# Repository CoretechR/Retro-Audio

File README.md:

# DIY Retro Audio Player

Inspired by 1980s tape recorders, this audio player was designed with ease of use and accessibility in mind. Despite its nostalgic appearance, it packs modern hardware. Powered by the ESP32, it plays music and audiobooks from a micro SD card, either on its internal speaker or though a headphone jack. A 2.8“ IPS screen and mechanical buttons make up the simplistic user interface. The software is built around the ESP32-audioI2S library by GitHub user Schreibfaul1.

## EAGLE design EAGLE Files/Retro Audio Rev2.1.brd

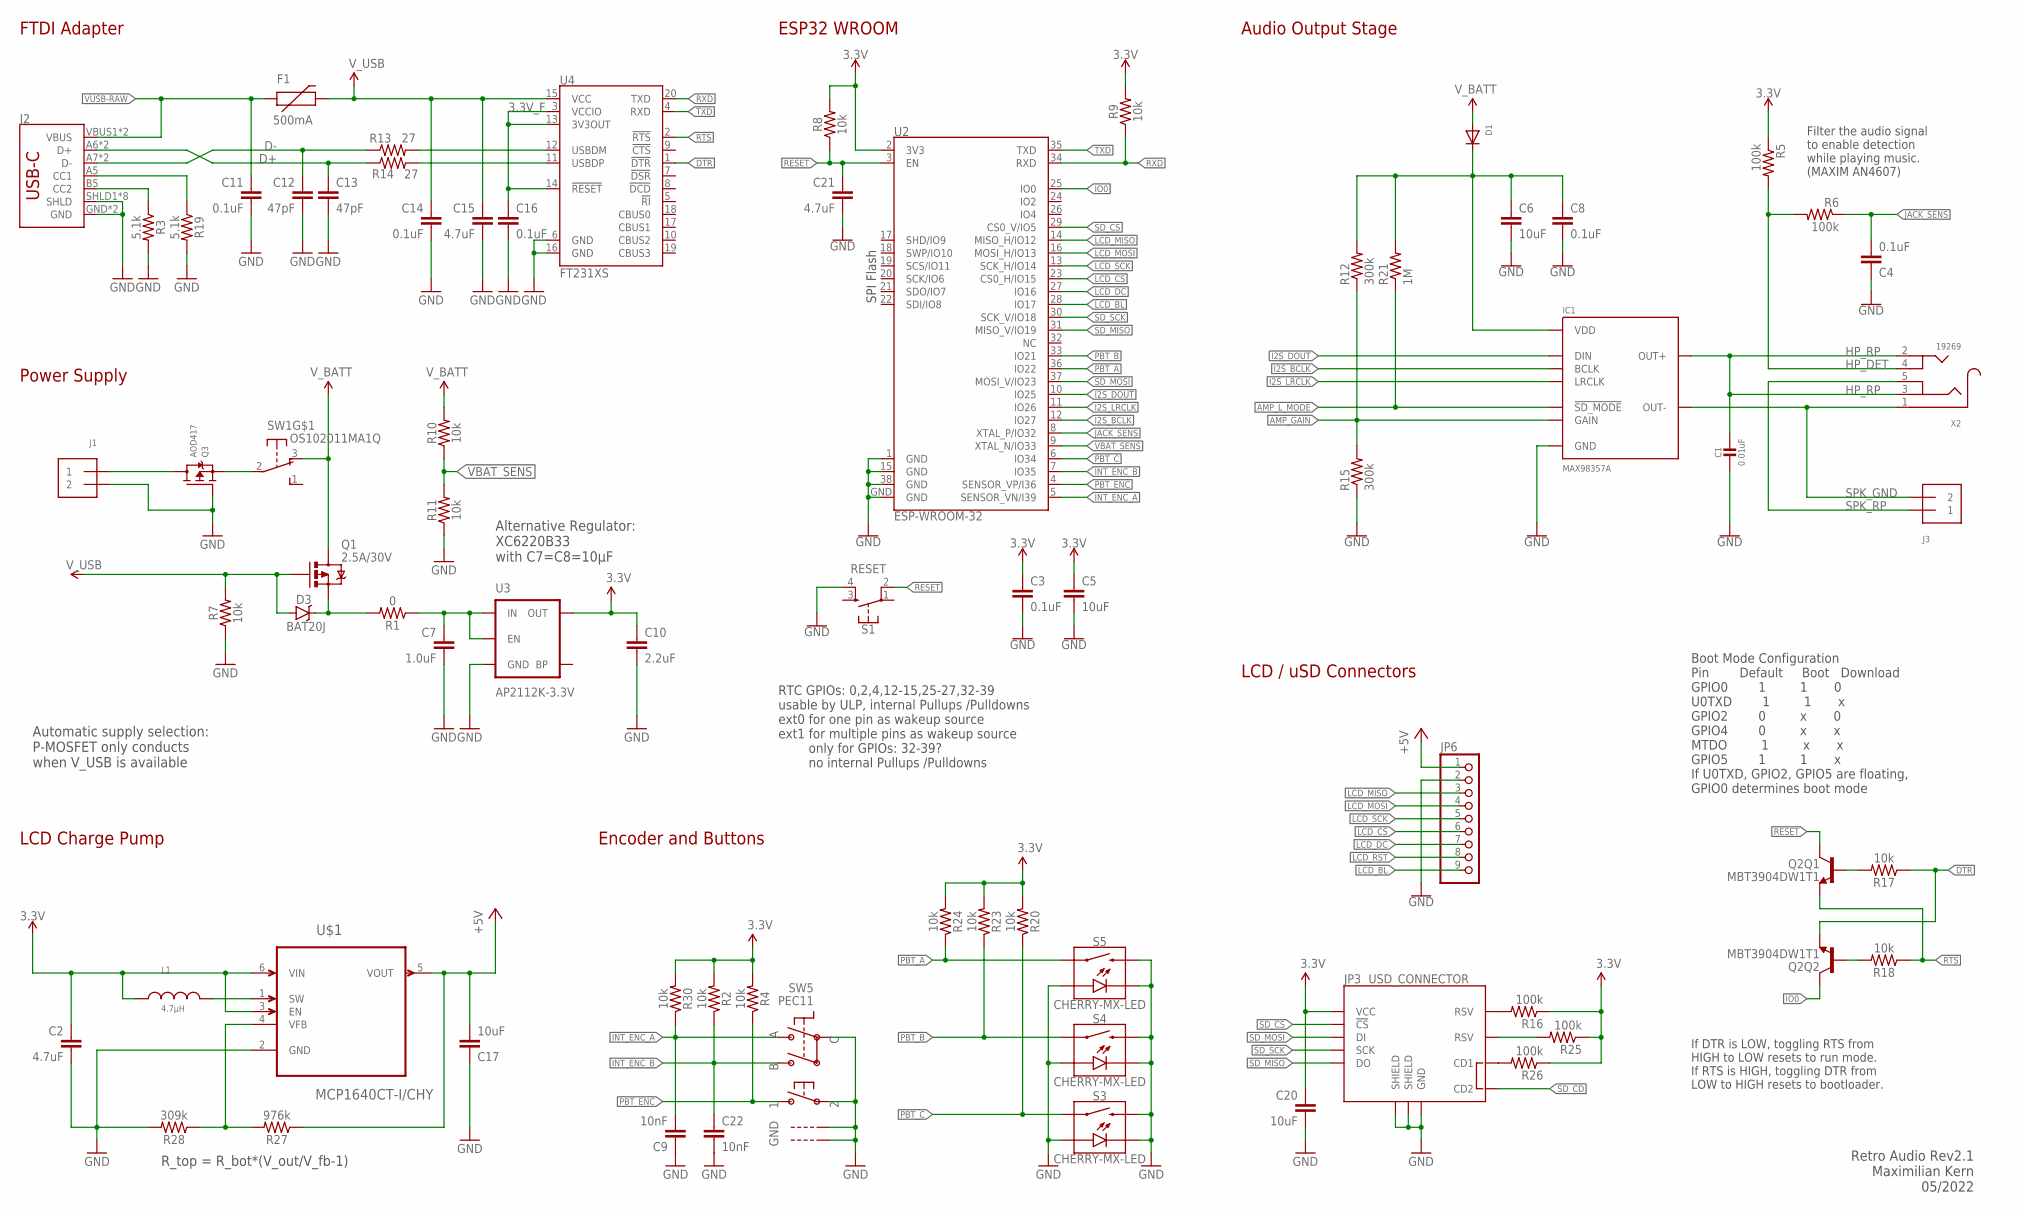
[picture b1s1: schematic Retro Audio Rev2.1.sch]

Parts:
C1: 0.01uF; 0603-NO
C2, C15, C21: 4.7uF; 0603-CAP
C3, C4, C8, C11, C14, C16: 0.1uF; 0603
C5, C6, C17, C20: 10uF; 0603
C7: 1.0uF; 0805
C9, C22: 10nF; 0805
C10: 2.2uF; 0805
C12, C13: 47pF; 0603
D1: DIODE_SOD-123FL; SOD-123FL
D3: BAT20J; SOD-323
F1: 500mA; PTC-1206
IC1: MAX98357A; TQFN-16
J1, J3: TERMBLOCK_1X2; TERMBLOCK_1X2-3.5MM
J2: USB_C16PIN; USB-C-16P
JP3: USD_CONNECTOR; MICRO-SD-SOCKET-PP
JP6: PINHD-1X9; 1X09
L1: 4.7µH; WE-TPC_2811/2813_OLD
Q1: 2.5A/30V; SOT23-3
Q2: MBT3904DW1T1; SC70-6
Q3: AOD417; TO252
R1: 0; 0603
R2, R4, R7, R8, R9, R10, R11, R17, R18, R20, R23, R24, R30: 10k; 0603
R3, R19: 5.1k; 0603
R5, R6, R16, R25, R26: 100k; R0603
R12, R15: 300k; R0603
R13, R14: 27; 0603
R21: 1M; R0603
R27: 976k; 0603
R28: 309k; 0603
S1: RESET; TACTILE_SWITCH_SMD_4.6X2.8MM
S3, S4, S5: CHERRY-MX-LED
SW1: OS102011MA1Q
SW5: PEC11; PEC11+SWITCH
U2: ESP-WROOM-32
U3: AP2112K-3.3V; SOT23-5
U4: FT231XS; SSOP20_L
U$1: MCP1640CT-I/CHY; SOT95P270X145-6N
X2: 19269; 4UCONN_19269

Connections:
3.3V: C2.1, C3.1, C5.1, C10.1, C20.1, JP3.VCC, L1.1, R2.2, R4.2, R5.1, R8.2, R9.2, R16.1, R20.2, R23.2, R24.2, R25.1, R26.1, R30.2, U2.2 (3V3), U3.5 (OUT), U$1.3 (EN), U$1.6 (VIN)
3.3V_F: C16.1, U4.3 (VCCIO), U4.13 (3V3OUT), U4.14 (!RESET)
+5V: C17.2, JP6.1, R27.1, U$1.5 (VOUT)
AMP_GAIN: IC1.P$2 (GAIN), R12.1, R15.2
AMP_L_MODE: IC1.P$4 (!SD_MODE), R21.1
B_VFB: R27.2, R28.1, U$1.4 (VFB)
D+: C13.1, J2.A6 (D+), J2.B6 (D+), R14.1
D-: C12.1, J2.A7 (D-), J2.B7 (D-), R13.1
DTR: Q2.1 (E), R17.1, U4.1 (!DTR)
GND: C1.2, C2.2, C3.2, C4.1, C5.2, C6.2, C7.2, C8.2, C9.1, C10.2, C11.2, C12.2, C13.2, C14.2, C15.2, C16.2, C17.1, C20.2, C21.2, C22.2, IC1.P$3 (GND), IC1.P$11 (GND), IC1.P$15 (GND), IC1.P$EP (GND), J1.2, J2.GND, J2.GND2 (GND), J2.SHLD1 (SHLD), J2.SHLD2 (SHLD), J2.SHLD3 (SHLD), J2.SHLD4 (SHLD), J2.SHLD5 (SHLD), J2.SHLD6 (SHLD), J2.SHLD7 (SHLD), J2.SHLD8 (SHLD), JP3.GND, JP3.GND1 (SHIELD), JP3.GND3 (SHIELD), JP6.2, Q3.1 (G), R3.2, R7.1, R11.1, R15.1, R19.2, R28.2, S1.4, S3.A, S3.K (C), S3.S2, S4.A, S4.K (C), S4.S2, S5.A, S5.K (C), S5.S2, SW5.P$2, SW5.P$C, SW5.P$GND1, SW5.P$GND2, U2.1 (GND), U2.15 (GND), U2.38 (GND), U2.GND, U3.2 (GND), U4.6 (GND), U4.16 (GND), U$1.2 (GND)
HP_DET: R5.2, R6.2, X2.4
HP_RP: C1.1, IC1.P$9 (OUT+), X2.2, X2.3
I2S_BCLK: IC1.P$16 (BCLK), U2.12 (IO27)
I2S_DOUT: IC1.P$1 (DIN), U2.10 (IO25)
I2S_LRCLK: IC1.P$14 (LRCLK), U2.11 (IO26)
INT_ENC_A: C9.2, R30.1, SW5.P$A, U2.5 (SENSOR_VN/I39)
INT_ENC_B: C22.1, R2.1, SW5.P$B, U2.7 (IO35)
IO0: Q2.6 (C), U2.25 (IO0)
JACK_SENS: C4.2, R6.1, U2.8 (XTAL_P/IO32)
LCD_BL: JP6.9, U2.28 (IO17)
LCD_CS: JP6.6, U2.23 (CS0_H/IO15)
LCD_DC: JP6.7, U2.27 (IO16)
LCD_MISO: JP6.3, U2.14 (MISO_H/IO12)
LCD_MOSI: JP6.4, U2.16 (MOSI_H/IO13)
LCD_RST: JP6.8
LCD_SCK: JP6.5, U2.13 (SCK_H/IO14)
unnamed: J1.1, Q3.3 (D)
unnamed: C7.1, R1.1, U3.1 (IN), U3.3 (EN)
unnamed: Q3.2 (S), SW1.2
unnamed: D3.C, Q1.2 (S), R1.2
unnamed: JP3.RSV1 (RSV), R16.2
unnamed: R13.2, U4.12 (USBDM)
unnamed: R14.2, U4.11 (USBDP)
unnamed: J2.A5 (CC1), R19.1
unnamed: Q2.5 (B), R17.2
unnamed: J2.B5 (CC2), R3.1
unnamed: Q2.2 (B), R18.2
unnamed: JP3.RSV2 (RSV), R25.2
unnamed: JP3.CD1, R26.2
unnamed: L1.2, U$1.1 (SW)
unnamed: C6.1, C8.1, D1.C, IC1.P$7 (VDD), IC1.P$8 (VDD), R12.2, R21.2
PBT_A: R24.1, S5.S1, U2.36 (IO22)
PBT_B: R23.1, S4.S1, U2.33 (IO21)
PBT_C: R20.1, S3.S1, U2.6 (IO34)
PBT_ENC: R4.1, SW5.P$1, U2.4 (SENSOR_VP/I36)
RESET: C21.1, Q2.3 (C), R8.1, S1.2, U2.3 (EN)
RTS: Q2.4 (E), R18.1, U4.2 (!RTS)
RXD: R9.1, U2.34 (RXD), U4.20 (TXD)
SD_CD: JP3.CD2
SD_CS: JP3.CS (!CS), U2.29 (CS0_V/IO5)
SD_MISO: JP3.DO, U2.31 (MISO_V/IO19)
SD_MOSI: JP3.DI, U2.37 (MOSI_V/IO23)
SD_SCK: JP3.SCLK (SCK), U2.30 (SCK_V/IO18)
SPK_GND: IC1.P$10 (OUT-), J3.2, X2.1
SPK_RP: J3.1, X2.5
TXD: U2.35 (TXD), U4.4 (RXD)
VBAT_SENS: R10.1, R11.2, U2.9 (XTAL_N/IO33)
VUSB-RAW: C11.1, F1.1, J2.VBUS1 (VBUS), J2.VBUS2 (VBUS)
V_BATT: D1.A, Q1.3 (D), R10.2, SW1.3 (O)
V_USB: C14.1, C15.1, D3.A, F1.2, Q1.1 (G), R7.2, U4.15 (VCC)

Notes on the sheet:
ESP32 WROOM
Boot Mode Configuration Pin Default Boot Download GPIO0 1 1 0 U0TXD 1 1 x GPIO2 0 x 0 GPIO4 0 x x MTDO 1 x x GPIO5 1 1 x If U0TXD, GPIO2, GPIO5 are floating, GPIO0 determines boot mode
If DTR is LOW, toggling RTS from HIGH to LOW resets to run mode. If RTS is HIGH, toggling DTR from LOW to HIGH resets to bootloader.
Power Supply
FTDI Adapter
Encoder and Buttons
LCD Charge Pump
RTC GPIOs: 0,2,4,12-15,25-27,32-39 usable by ULP, internal Pullups /Pulldowns ext0 for one pin as wakeup source ext1 for multiple pins as wakeup source only for GPIOs: 32-39? no internal Pullups /Pulldowns
SPI Flash
Retro Audio Rev2.1 Maximilian Kern 05/2022
Alternative Regulator: XC6220B33 with C7=C8=10µF
Automatic supply selection: P-MOSFET only conducts when V_USB is available
Audio Output Stage
R_top = R_bot*(V_out/V_fb-1)
LCD / uSD Connectors
Filter the audio signal to enable detection while playing music. (MAXIM AN4607)

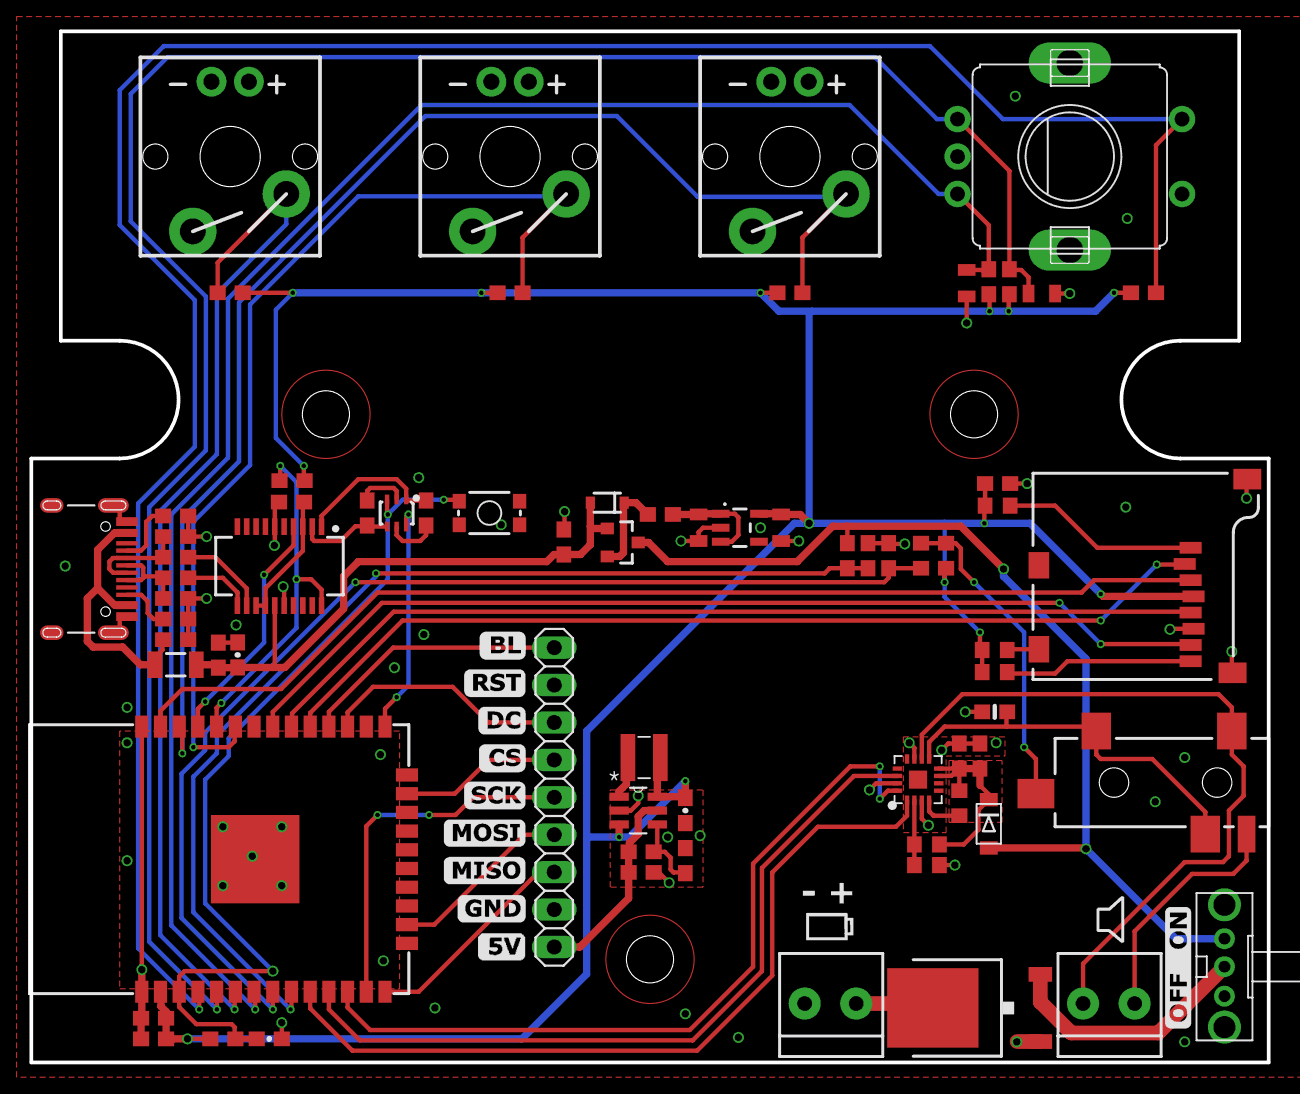
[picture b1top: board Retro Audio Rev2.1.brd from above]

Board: 2 copper layers, 84.0 x 70.0 mm, 72 parts (0 on the bottom side), 58 nets.

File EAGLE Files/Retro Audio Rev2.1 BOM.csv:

Qty,Value,Device,Package,Parts,Description,MPN,Supplier,Link
1,,DIODE_SOD-123FL,SOD-123FL,D1,Diode,BAS116H;115,Nexperia,https://www.mouser.de/ProductDetail/771-BAS116H115
1,,PINHD-1X9,1X09,JP6,PIN HEADER,,,
2,,TERMBLOCK_1X2,TERMBLOCK_1X2-3.5MM,J1; J3,3.5mm Terminal block,6;91103E+11,Würth Elektronik,https://www.mouser.de/ProductDetail/710-691103110002
1,,USB_C16PIN,USB-C-16P,J2,USB Type C 16Pin Connector,USB4125-GF-A,GCT,https://www.mouser.de/ProductDetail/640-USB4125-GF-A
1,0,10KOHM-0603-1/10W-1%,603,R1,10kO resistor,,,
6,0.1uF,0.1UF-0603-25V-(+80/-20%),603,C3; C4; C8; C11; C14; C16,0.1µF ceramic capacitors,,,
1,1.0uF,1.0UF-0805-25V-(+80/-20%),805,C7,1µF ceramic capacitors,,,
5,100k,R-US_R0603,R0603,R5; R6; R16; R25; R26,RESISTOR; American symbol,,,
13,10k,10KOHM-0603-1/10W-1%,603,R2; R4; R7; R8; R9; R10; R11; R17; R18; R20; R23; R24; R30,10kO resistor,,,
2,10nF,1.0UF-0805-25V-(+80/-20%),805,C9; C22,1µF ceramic capacitors,,,
3,10uF,10UF-0603-6.3V-20%,603,C5; C6; C20,10.0µF ceramic capacitors,,,
1,10uF,47PF-0603-50V-5%,603,C17,47pF ceramic capacitors,,,
1,19269,AUDIO_3.5MMJACK,4UCONN_19269,X2,3.5MM Audio Jack,SJ2-3593D-SMT-TR,CUI,https://www.mouser.de/ProductDetail/490-SJ2-3593D-SMT-TR
1,1M,R-US_R0603,R0603,R21,RESISTOR; American symbol,,,
1,2.2uF,1.0UF-0805-25V-(+80/-20%),805,C10,1µF ceramic capacitors,,,
1,2.5A/30V,MOSFET-PCHANNELDMG2307L,SOT23-3,Q1,Generic PMOSFET,DMG2307L-7,Diodes Inc,https://www.mouser.de/ProductDetail/621-DMG2307L-7
2,27,27OHM1/10W1%(0603)0603-RES,603,R13; R14,RES-09334,,,
1,309k,10KOHM-0603-1/10W-1%,603,R28,10kO resistor,,,
3,4.7uF,4.7UF-6.3V-10%(0603)0603,0603-CAP,C2; C15; C21,CAP-08280,,,
1,4.7µH,WE-TPC_2813_744029004,WE-TPC_2811/2813_OLD,L1,SMD Shielded Tiny Power Inductor,744029004,Würth Elektronik,https://www.digikey.de/en/products/detail/w%C3%BCrth-elektro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
2,47pF,47PF-0603-50V-5%,603,C12; C13,47pF ceramic capacitors,,,
2,5.1k,10KOHM-0603-1/10W-1%,603,R3; R19,10kO resistor,,,
1,500mA,PTCSMD,PTC-1206,F1,Resettable Fuse PTC,1206L050/15YR,Littelfuse,https://www.mouser.de/ProductDetail/576-1206L050-15YR
1,976k,10KOHM-0603-1/10W-1%,603,R27,10kO resistor,,,
1,AOD417,MOSFET-PTO252,TO252,Q3,P-Channel Mosfet,AOD417,Alpha&Omega,https://www.digikey.de/de/products/detail/alpha-omega-semico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
1,AP2112K-3.3V,V_REG_LDOSMD,SOT23-5,U3,Voltage Regulator LDO,AP2112K-3.3TRG1,Diodes Inc,https://www.mouser.de/ProductDetail/621-AP2112K-3.3TRG1
1,BAT20J,DIODE-SCHOTTKY-BAT20J,SOD-323,D3,Schottky diodes in SFE's production catalog,BAT20JFILM,STM,https://www.mouser.de/ProductDetail/511-BAT20JFILM
3,CHERRY-MX-LED,CHERRY-MX-LED,CHERRY-MX-LED,S3; S4; S5,,MX1A-E1NW,Cherry,https://www.mouser.de/ProductDetail/540-MX1A-E1NW
1,ESP-WROOM-32,ESP-WROOM-32,ESP-WROOM-32,U2,,ESP32-WROOM-32D-N4,Espressif,https://www.mouser.de/ProductDetail/356-ESP32WROOM-32D
1,FT231XS,FT231XS,SSOP20_L,U4,FTDI FT231X Full Speed USB to Full-handshake UART,FT231XS-R,FTDI,https://www.mouser.de/ProductDetail/895-FT231XS-R
1,MAX98357A,MAX98357A,TQFN-16,IC1,I2S DAC 3.2W (4-8ohm),MAX98357AETE+T,Maxim,https://www.mouser.de/ProductDetail/700-MAX98357AETE%2bT
1,MBT3904DW1T1,MBT3904DW1T1,SC70-6,Q2,MBT3904DW1 Dual NPN Transistors,MBT3904DW1T1G,OnSemi,https://www.mouser.de/ProductDetail/863-MBT3904DW1T1G
1,MCP1640CT-I/CHY,MCP1640CT-I/CHY,SOT95P270X145-6N,U$1,Synchronous Boost Regulator,MCP1640CT-I/CHY,Microchip,https://www.digikey.de/de/products/detail/microchip-technolo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
1,OS102011MA1Q,OS102011MA1Q,OS102011MA1Q,SW1,OS10201MA1Q through-hole right angle switch,OS102011MA1QN1,C&K,https://www.mouser.de/ProductDetail/611-OS102011MA1QN1
1,PEC11,ENCODER_PLUS_SWITCH_BOURNS_PEC11,PEC11+SWITCH,SW5,Rotary Encoder with Built-In Switch,EC12E20-24P24C-SW,SRPassives,https://www.tme.eu/de/details/ec12e20-24p24c-sw/inkrementale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
1,RESET,MOMENTARY-SWITCH-SPST-2-SMD-4.6X2.8MM,TACTILE_SWITCH_SMD_4.6X2.8MM,S1,Momentary Switch (Pushbutton) - SPST - Two Circuits,KMR211GLFS,C&K,https://www.mouser.de/ProductDetail/611-KMR211G-LFS
1,USD_CONNECTOR,USD_CONNECTOR,MICRO-SD-SOCKET-PP,JP3,microSD Socket,MEM2061-01-188-00-A,GCT,https://www.mouser.de/ProductDetail/640-MEM20610118800A
,,,,,,,,
Extra components that are not part of the PCB:,,,,,,,,
3,,Sparkfun Keycaps,,,,PRT-15305,Sparkfun,https://www.mouser.de/ProductDetail/474-PRT-15305
1,,Keystone Battery Holder,,,,2478,Keystone,https://www.mouser.de/ProductDetail/534-2478
1,,Speaker,,,,CDS-40304-L100,CUI Devices,https://www.mouser.de/ProductDetail/490-CDS-40304-L100
1,,"2.8"" 320x240px Display",,,,16446,Waveshare,https://www.waveshare.com/2.8inch-resistive-touch-lcd.htm

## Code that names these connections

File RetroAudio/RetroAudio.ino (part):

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#define WIDTH    320
#define HEIGHT   240

#define I2S_DOUT     25
#define I2S_BCLK     27
#define I2S_LRC      26

#define SD_CS        5
#define SD_MOSI      23
#define SD_MISO      19
#define SD_SCK       18

//#define LCD_DC       16 // defined in TFT_eSPI User_Setup.h
//#define LCD_CS       15
//#define LCD_MOSI     13
//#define LCD_SCK      14
//#define LCD_MISO     12
#define LCD_BL     17 

#define ABUT      22
#define BBUT      21
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#define ENCINTB   35
#define ENCBUT    36

#define JACK_SENS 32
#define VBAT_SENS 33

Button buttonA(ABUT, false, true, 5); //pin, pullup, invert, debounce
Button buttonB(BBUT, false, true, 5);
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
void setup() {

  pinMode(LCD_BL, OUTPUT);
  pinMode(ABUT, INPUT);
  pinMode(BBUT, INPUT);
  pinMode(CBUT, INPUT);
  pinMode(ENCINTA, INPUT);
  pinMode(ENCINTB, INPUT);
  pinMode(ENCBUT, INPUT);
  pinMode(SD_CS, OUTPUT);

  attachInterrupt(ENCINTA, isr_enca, CHANGE);
  attachInterrupt(ENCINTB, isr_encb, CHANGE);
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  //create a folder to store save files
  if(!SD.exists("/persistence"))  SD.mkdir("/persistence");    

  audio.setPinout(I2S_BCLK, I2S_LRC, I2S_DOUT);
  restoreVolume();
  
  audio.setPinout(I2S_BCLK, I2S_LRC, I2S_DOUT);
  audio.setVolume(volume_hp);

  audio.connecttoSD(tracks[currentTrackNum].c_str(), restorePosition(tracks[currentTrackNum]));
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
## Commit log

2022-07-14 Gerber RS274X files added
2022-08-29 BOM Updates with more Links and Details
2022-08-29 BOM updated with more Details
2022-09-24 Updated to show unused parts
2022-12-28 Bug fixes, power saving and optimizations
    - Audio decoding in loop instead of thread -> no more crashes while fast forwarding
    - Auto screen off after 15 seconds
2023-03-06 added list of software and library versions used

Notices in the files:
parts and their libraries:
SparkFun-RF: Licensing: Creative Commons ShareAlike 4.0 International - https://creativecommons.org/licenses/by-sa/4.0
SparkFun-DigitalIC: Licensing: CC v3.0 Share-Alike You are welcome to use this library for commercial purposes.
EMCComponents: Copyright: Würth Elektronik
